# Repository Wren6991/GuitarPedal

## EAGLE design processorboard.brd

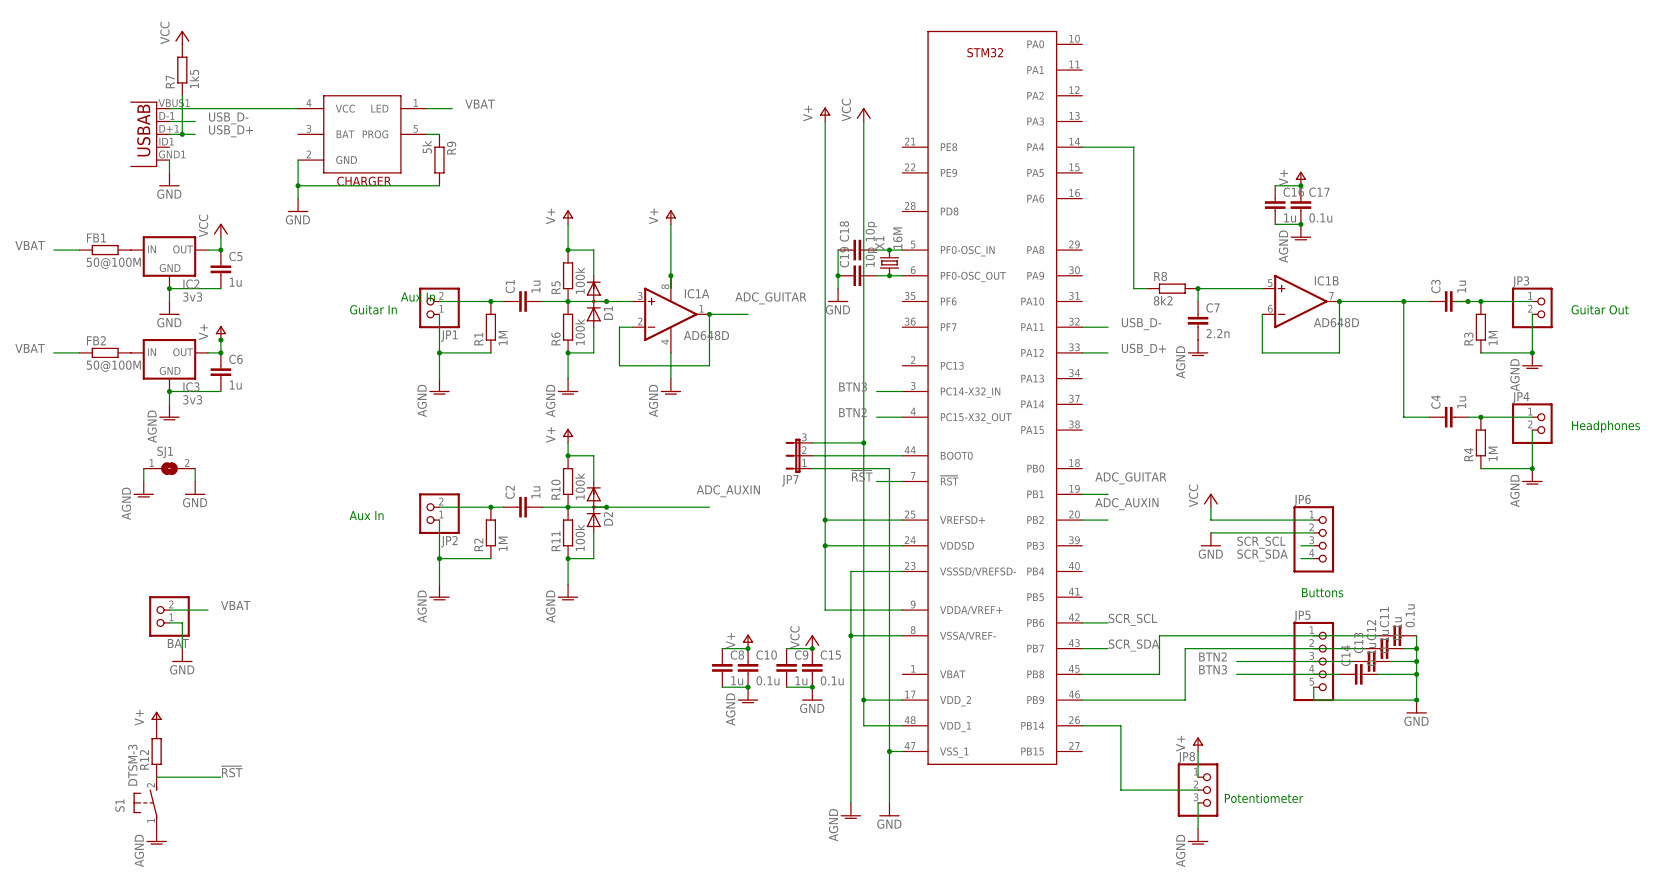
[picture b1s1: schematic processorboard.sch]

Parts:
BAT: PINHD-1X2; 1X02
C1, C2, C3, C4, C5, C6, C8, C9, C16: 1u; C0805
C7: 2.2n; C0805
C10, C11, C12, C13, C14, C15, C17: 0.1u; C0805
C18, C19: 10p; C0805
D1, D2: DIODE_2CACA-SOT23; SOT23
FB1, FB2: 50@100M; R0805
IC1: AD648D; SO08
IC2, IC3: 3v3; SOT23
JP1, JP2, JP3, JP4: PINHD-1X2; 1X02
JP5: PINHD-1X5; 1X05
JP6: PINHD-1X4; 1X04
JP7: JP2E; JP2
JP8: PINHD-1X3; 1X03
R1, R2, R3, R4: 1M; R0805
R5, R6, R10, R11: 100k; R0805
R7: 1k5; R0805
R8: 8k2; R0805
R9: 5k; R0805
R12: R-EU_R0805; R0805
S1: DTSM-3
SJ1: SJ
U1: USB""; USB-MICRO-SMD
U$1: STM32F373CBT6; LQFP48
U$2: LI_CHARGER; SOT23-5L
X1: 16M; HC49UP

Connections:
!RST: R12.1, S1.2, U$1.7 (!RST)
ADC_AUXIN: C2.2, D2.3 (AC), R10.1, R11.2, U$1.20 (PB2)
ADC_GUITAR: IC1.1 (OUT), IC1.2 (-IN), U$1.19 (PB1)
AGND: C6.2, C7.2, C8.2, C10.2, C16.2, C17.2, D1.1 (A), D2.1 (A), IC1.4 (V-), IC3.1 (GND), JP1.1, JP2.1, JP3.2, JP4.2, JP8.3, R1.1, R2.1, R3.1, R4.1, R6.1, R11.1, S1.1, SJ1.1, U$1.8 (VSSA/VREF-), U$1.23 (VSSSD/VREFSD-)
BTN0: C11.1, JP5.1, U$1.45 (PB8)
BTN1: C12.1, JP5.2, U$1.46 (PB9)
BTN2: C13.1, JP5.3, U$1.4 (PC15-X32_OUT)
BTN3: C14.1, JP5.4, U$1.3 (PC14-X32_IN)
DAC_GUITAR: R8.1, U$1.14 (PA4)
DAC_GUITAR_FILT: C7.1, IC1.5 (+IN), R8.2
GND: BAT.1, C5.2, C9.2, C11.2, C12.2, C13.2, C14.2, C15.2, C18.1, C19.1, IC2.1 (GND), JP5.5, JP6.2, JP7.1, R9.2, SJ1.2, U1.GND1 (GND), U$1.47 (VSS_1), U$2.2 (GND)
unnamed: C3.2, JP3.1, R3.2
unnamed: C4.2, JP4.1, R4.2
unnamed: C2.1, JP2.2, R2.2
unnamed: JP7.2, U$1.44 (BOOT0)
unnamed: C1.1, JP1.2, R1.2
unnamed: C1.2, D1.3 (AC), IC1.3 (+IN), R5.1, R6.2
unnamed: C19.2, U$1.6 (PF0-OSC_OUT), X1.1
unnamed: JP8.2, U$1.26 (PB14)
unnamed: FB1.2, IC2.3 (IN)
unnamed: C3.1, C4.1, IC1.6 (-IN), IC1.7 (OUT)
unnamed: R9.1, U$2.5 (PROG)
unnamed: FB2.2, IC3.3 (IN)
unnamed: C18.2, U$1.5 (PF0-OSC_IN), X1.2
SCR_SCL: JP6.3, U$1.42 (PB6)
SCR_SDA: JP6.4, U$1.43 (PB7)
USB_D+: R7.1, U1.D+1 (D+), U$1.33 (PA12)
USB_D-: U1.D-1 (D-), U$1.32 (PA11)
V+: C6.1, C8.1, C10.1, C16.1, C17.1, D1.2 (C), D2.2 (C), IC1.8 (V+), IC3.2 (OUT), JP8.1, R5.2, R10.2, R12.2, U$1.9 (VDDA/VREF+), U$1.24 (VDDSD), U$1.25 (VREFSD+)
VBAT: BAT.2, FB1.1, FB2.1, U$2.1 (LED)
VCC: C5.1, C9.1, C15.1, IC2.2 (OUT), JP6.1, JP7.3, R7.2, U$1.17 (VDD_2), U$1.48 (VDD_1)
VUSB: U1.VBUS1 (VBUS), U$2.4 (VCC)

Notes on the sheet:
Guitar In
Aux In
Guitar Out
Headphones
Buttons
Potentiometer

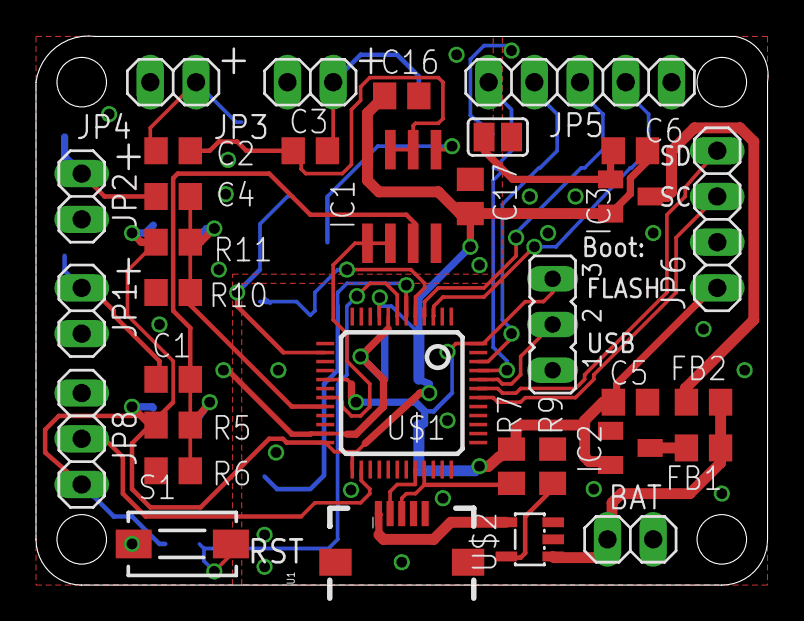
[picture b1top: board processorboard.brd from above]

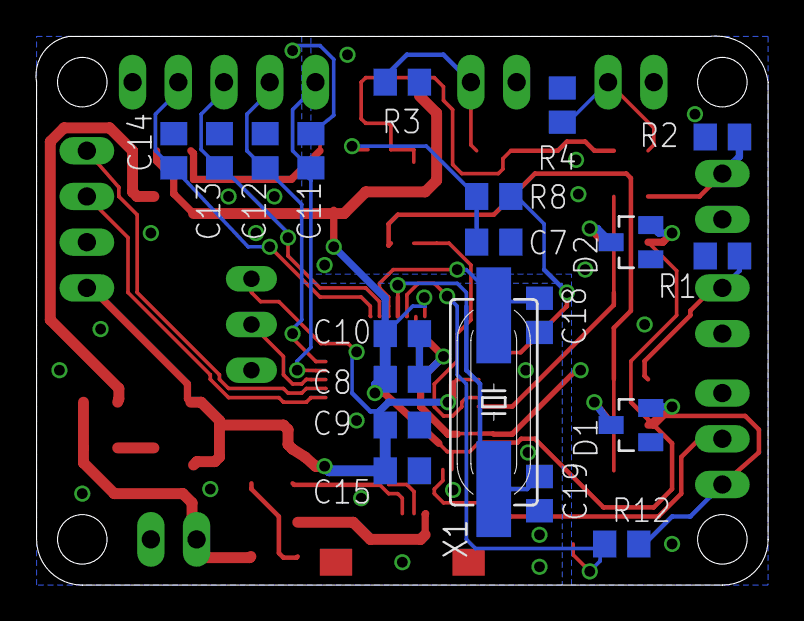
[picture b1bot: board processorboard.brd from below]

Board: 2 copper layers, 40.7 x 30.5 mm, 53 parts (20 on the bottom side), 32 nets.

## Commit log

2015-11-23 added license
